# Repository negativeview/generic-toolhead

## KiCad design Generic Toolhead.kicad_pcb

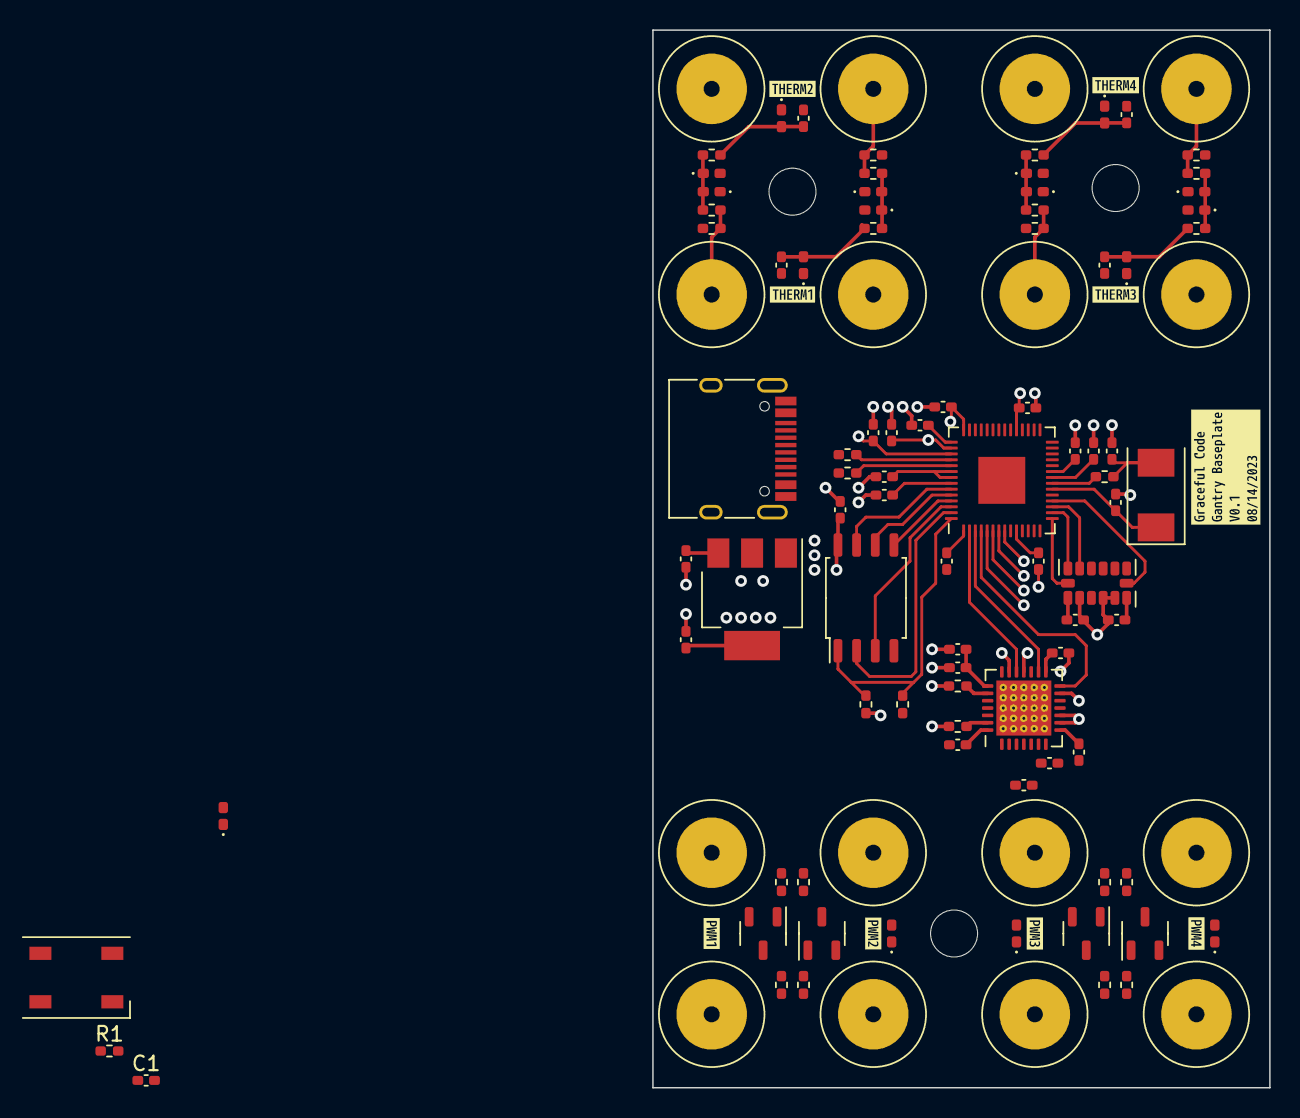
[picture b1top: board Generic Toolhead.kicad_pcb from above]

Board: 2 copper layers, 42.0 x 72.0 mm, 111 parts (0 on the bottom side), 55 nets.

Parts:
C1: C_Small; C_0402_1005Metric_Pad0.74x0.62mm_HandSolder
C2, C11, C12, C13, C14: 0u1; C_0402_1005Metric_Pad0.74x0.62mm_HandSolder
C3, C17, C20: 1u; C_0402_1005Metric_Pad0.74x0.62mm_HandSolder
C4: 100u; C_0402_1005Metric_Pad0.74x0.62mm_HandSolder
C5, C6, C8, C15, C16, C18, C19, C21, C22, C23, C24, C25, C28: 100n; C_0402_1005Metric_Pad0.74x0.62mm_HandSolder
C7: 100n 16V; C_0402_1005Metric_Pad0.74x0.62mm_HandSolder
C9, C10: 2u2 6V3; C_0402_1005Metric_Pad0.74x0.62mm_HandSolder
C26, C27: 10u; C_0402_1005Metric_Pad0.74x0.62mm_HandSolder
C29, C30: 27p; C_0402_1005Metric_Pad0.74x0.62mm_HandSolder
D1: WS2812B; LED_WS2812B_PLCC4_5.0x5.0mm_P3.2mm
D2, D5, D8, D11: D_TVS; D_0402_1005Metric_Pad0.77x0.64mm_HandSolder
D3, D4, D6, D7, D9, D10, D12, D13, D14, D15, D16, D17: D_Small; D_0402_1005Metric_Pad0.77x0.64mm_HandSolder
J2: USB_C_Receptacle_USB2.0; USB_C_Receptacle_HRO_TYPE-C-31-M-12
Q1, Q2, Q3, Q4: LND150; SOT-23-3
R1, R2, R3: R_Small; R_0402_1005Metric_Pad0.72x0.64mm_HandSolder
R4, R5, R7, R8, R10, R11, R13, R14: 2k37; R_0402_1005Metric_Pad0.72x0.64mm_HandSolder
R6, R9, R12, R15: 4k7; R_0402_1005Metric_Pad0.72x0.64mm_HandSolder
R16, R18, R20, R22: 10; R_0402_1005Metric_Pad0.72x0.64mm_HandSolder
R17, R19, R21, R23: 100k; R_0402_1005Metric_Pad0.72x0.64mm_HandSolder
R24, R25: 27_4; R_0402_1005Metric_Pad0.72x0.64mm_HandSolder
R26, R28: 1k; R_0402_1005Metric_Pad0.72x0.64mm_HandSolder
R27: 10k; R_0402_1005Metric_Pad0.72x0.64mm_HandSolder
TP1, TP2, TP3, TP4, TP5, TP6, TP7, TP8, TP9, TP10, TP11, TP12, TP13, TP14, TP15, TP16: TestPoint; Pogo Pin
U1: ADXL345; LGA-14_3x5mm_P0.8mm_LayoutBorder1x6y
U2: RP2040; QFN-56-1EP_7x7mm_P0.4mm_EP3.2x3.2mm
U3: TMC2209; QFN-28-1EP_5x5mm_P0.5mm_EP3.75x3.75mm_ThermalVias
U4: AP1117-33; SOT-223-3_TabPin2
U5: W25Q128JVS; SOIC-8_5.23x5.23mm_P1.27mm
Y1: Crystal; Crystal_SMD_0603-2Pin_6.0x3.5mm
kibuzzard-64D9AE6A: G***; kibuzzard-64D9AE6A
kibuzzard-64D9AE25: G***; kibuzzard-64D9AE25
kibuzzard-64D9AE55: G***; kibuzzard-64D9AE55
kibuzzard-64D9AE78: G***; kibuzzard-64D9AE78
kibuzzard-64D9D5AA: G***; kibuzzard-64D9D5AA
kibuzzard-64D9D5C0: G***; kibuzzard-64D9D5C0
kibuzzard-64D9D5CE: G***; kibuzzard-64D9D5CE
kibuzzard-64D9D5DA: G***; kibuzzard-64D9D5DA
kibuzzard-64DA0FFB: G***; kibuzzard-64DA0FFB

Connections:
+1V1: C15.1, C16.1, C17.1, U2.23 (DVDD), U2.45 (VREG_VOUT), U2.50 (DVDD)
+3V3: C2.1, C3.1, C8.1, C18.1, C19.1, C20.1, C21.1, C22.1, C23.1, C24.1, C25.1, C27.1, C28.1, D4.1 (K), D7.1 (K), D10.1 (K), D13.1 (K), R6.1, R9.1, R12.1, R15.1, R27.1, U1.1 (VDD_IO), U1.6 (VS), U2.1 (IOVDD), U2.10 (IOVDD), U2.22 (IOVDD), U2.33 (IOVDD), U2.42 (IOVDD), U2.43 (ADC_AVDD), U2.44 (VREG_IN), U2.48 (USB_VDD), U2.49 (IOVDD), U3.15 (VCC_IO), U4.2 (VO), U5.8 (VCC)
+24V: C1.1, C4.1, C5.1, C6.1, C7.1, D14.1 (K), D15.1 (K), D16.1 (K), D17.1 (K), R1.2, U3.22 (VM), U3.28 (VM)
/ADXL/CS: U1.7 (NCS), U2.18 (GPIO15)
/ADXL/SCL: U1.14 (SCL), U2.15 (GPIO12)
/ADXL/SDA: U1.13 (SDA), U2.16 (GPIO13)
/ADXL/SDO: U1.12 (SDO), U2.17 (GPIO14)
/MOSFET Driver1/INPUT: R18.1, U2.6 (GPIO4)
/MOSFET Driver2/INPUT: R20.1, U2.7 (GPIO5)
/MOSFET Driver3/INPUT: R22.1, U2.8 (GPIO6)
/MOSFET Driver/INPUT: R16.1, U2.5 (GPIO3)
/Motor Driver/DIR: U2.2 (GPIO0), U3.19 (DIR)
/Motor Driver/STEP: U2.3 (GPIO1), U3.16 (STEP)
/Motor Driver/UART: U2.4 (GPIO2), U3.14 (PDN_UART)
/Oscillator/XIN: C29.2, U2.20 (XIN), Y1.1
/Oscillator/XOUT: R28.2, U2.21 (XOUT)
/QSPI_SCLK: U2.52 (QSPI_SCLK), U5.6 (CLK)
/QSPI_SD0: U2.53 (QSPI_SD0), U5.5 (DI(IO0))
/QSPI_SD1: U2.55 (QSPI_SD1), U5.2 (DO(IO1))
/QSPI_SD2: U2.54 (QSPI_SD2), U5.3 (IO2)
/QSPI_SD3: U2.51 (QSPI_SD3), U5.7 (IO3)
/QSPI_SS: R26.2, R27.2, U2.56 (QSPI_SS), U5.1 (~CS)
/Thermistor1/TH_MCU: C12.2, D5.2 (A2), R7.2, U2.40 (GPIO28_ADC2)
/Thermistor2/TH_MCU: C13.2, D8.2 (A2), R10.2, U2.39 (GPIO27_ADC1)
/Thermistor3/TH_MCU: C14.2, D11.2 (A2), R13.2, U2.38 (GPIO26_ADC0)
/Thermistor/TH_MCU: C11.2, D2.2 (A2), R4.2, U2.41 (GPIO29_ADC3)
/USB_DM: J2.A7 (D-), J2.B7 (D-), R25.2
/USB_DP: J2.A6 (D+), J2.B6 (D+), R24.1
/VBUS: C26.1, J2.A4 (VBUS), J2.A9 (VBUS), J2.B4 (VBUS), J2.B9 (VBUS), U4.3 (VI)
GND: C1.2, C2.2, C3.2, C4.2, C5.2, C6.2, C8.2, C10.2, C11.1, C12.1, C13.1, C14.1, C15.2, C16.2, C17.2, C18.2, C19.2, C20.2, C21.2, C22.2, C23.2, C24.2, C25.2, C26.2, C27.2, C28.2, C29.1, C30.1, D2.1 (A1), D3.2 (A), D5.1 (A1), D6.2 (A), D8.1 (A1), D9.2 (A), D11.1 (A1), D12.2 (A), J2.A1 (GND), J2.A12 (GND), J2.B1 (GND), J2.B12 (GND), Q1.3 (S), Q2.3 (S), Q3.3 (S), Q4.3 (S), R2.2, R3.2, R17.1, R19.1, R21.1, R23.1, TP2.1, TP4.1, TP6.1, TP8.1, TP10.1, TP12.1, TP14.1, TP16.1, U1.2 (GND), U1.4 (GND), U1.5 (GND), U3.2 (ENN), U3.3 (GND), U3.9 (MS1_ADO), U3.10 (MS2_AD1), U3.13 (CLK), U3.18 (GND), U3.20 (STDBY), U3.29 (EPAD), U4.1 (GND)
unnamed: C7.2, U3.6 (VCP)
unnamed: C9.1, U3.4 (CPO)
unnamed: C9.2, U3.5 (CPI)
unnamed: C10.1, U3.8 (5VOUT)
unnamed: C30.2, R28.1, Y1.2
unnamed: D3.1 (K), D4.2 (A), R4.1, R5.2
unnamed: D6.1 (K), D7.2 (A), R7.1, R8.2
unnamed: D9.1 (K), D10.2 (A), R10.1, R11.2
unnamed: D12.1 (K), D13.2 (A), R13.1, R14.2
unnamed: D14.2 (A), Q1.2 (D), TP9.1
unnamed: D15.2 (A), Q2.2 (D), TP11.1
unnamed: D16.2 (A), Q3.2 (D), TP13.1
unnamed: D17.2 (A), Q4.2 (D), TP15.1
unnamed: Q1.1 (G), R16.2, R17.2
unnamed: Q2.1 (G), R18.2, R19.2
unnamed: Q3.1 (G), R20.2, R21.2
unnamed: Q4.1 (G), R22.2, R23.2
unnamed: R2.1, U3.23 (BRA)
unnamed: R3.1, U3.27 (BRB)
unnamed: R5.1, R6.2, TP1.1
unnamed: R8.1, R9.2, TP3.1
unnamed: R11.1, R12.2, TP5.1
unnamed: R14.1, R15.2, TP7.1
unnamed: R24.2, U2.47 (USB_DP)
unnamed: R25.1, U2.46 (USB_DM)

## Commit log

2023-05-01 First very fast pass.
2023-08-14 Big update.
2023-08-14 Forgot these bits.
2023-08-14 More big changes. Almost entirely done.
2023-08-14 Far better layout.
2023-08-14 After further research, fp-lib-table should probably be comitted.
